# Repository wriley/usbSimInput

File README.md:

# usbSimInput

This project is a 128 button USB HID joystick based on an open source USB game controller adapter by Raphaël Assénat.
http://www.raphnet-tech.com/products/nes2usb/

I use it to interface a lot of switches to a flight simulator but you could use it for anything that requires a lot of buttons.

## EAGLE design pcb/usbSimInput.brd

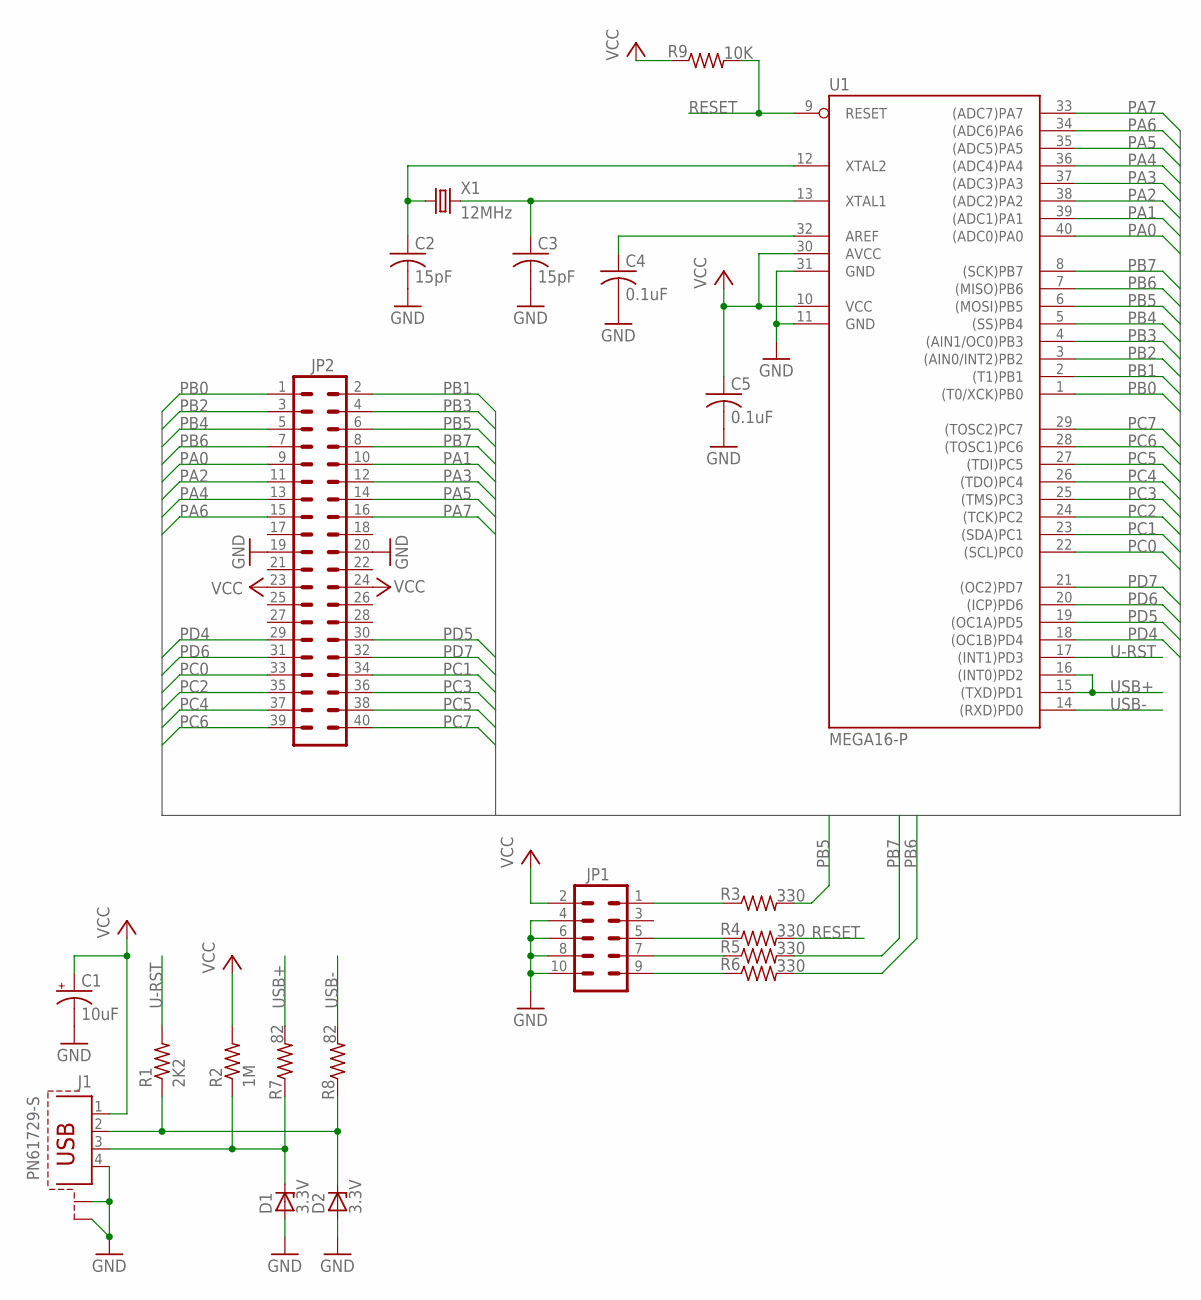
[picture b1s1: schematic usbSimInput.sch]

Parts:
C1: 10uF; E2,5-5
C2, C3: 15pF; C025-024X044
C4, C5: 0.1uF; C050-025X075
D1, D2: 3.3V; ZDIO-5
J1: PN61729-S
JP1: ML10
JP2: MA20-2
R1: 2K2; 0207/7
R2: 1M; 0207/7
R3, R4, R5, R6: 330; 0207/7
R7, R8: 82; 0207/7
R9: 10K; 0207/7
U1: MEGA16-P; DIL40
X1: 12MHz; HC49U-V

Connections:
GND: C1.-, C2.2, C3.2, C4.2, C5.2, D1.A, D2.A, J1.4, J1.S1, J1.S2, JP1.4, JP1.6, JP1.8, JP1.10, JP2.19, JP2.20, U1.11 (GND), U1.31 (GND)
unnamed: JP1.1, R3.1
unnamed: JP1.5, R4.1
unnamed: JP1.7, R5.1
unnamed: JP1.9, R6.1
unnamed: C3.1, U1.13 (XTAL1), X1.2
unnamed: C2.1, U1.12 (XTAL2), X1.1
unnamed: D2.C, J1.2, R1.1, R8.1
unnamed: C4.1, U1.32 (AREF)
unnamed: D1.C, J1.3, R2.1, R7.1
PA0: JP2.9, U1.40 ((ADC0)PA0)
PA1: JP2.10, U1.39 ((ADC1)PA1)
PA2: JP2.11, U1.38 ((ADC2)PA2)
PA3: JP2.12, U1.37 ((ADC3)PA3)
PA4: JP2.13, U1.36 ((ADC4)PA4)
PA5: JP2.14, U1.35 ((ADC5)PA5)
PA6: JP2.15, U1.34 ((ADC6)PA6)
PA7: JP2.16, U1.33 ((ADC7)PA7)
PB0: JP2.1, U1.1 ((T0/XCK)PB0)
PB1: JP2.2, U1.2 ((T1)PB1)
PB2: JP2.3, U1.3 ((AIN0/INT2)PB2)
PB3: JP2.4, U1.4 ((AIN1/OC0)PB3)
PB4: JP2.5, U1.5 ((SS)PB4)
PB5: JP2.6, R3.2, U1.6 ((MOSI)PB5)
PB6: JP2.7, R6.2, U1.7 ((MISO)PB6)
PB7: JP2.8, R5.2, U1.8 ((SCK)PB7)
PC0: JP2.33, U1.22 ((SCL)PC0)
PC1: JP2.34, U1.23 ((SDA)PC1)
PC2: JP2.35, U1.24 ((TCK)PC2)
PC3: JP2.36, U1.25 ((TMS)PC3)
PC4: JP2.37, U1.26 ((TDO)PC4)
PC5: JP2.38, U1.27 ((TDI)PC5)
PC6: JP2.39, U1.28 ((TOSC1)PC6)
PC7: JP2.40, U1.29 ((TOSC2)PC7)
PD4: JP2.29, U1.18 ((OC1B)PD4)
PD5: JP2.30, U1.19 ((OC1A)PD5)
PD6: JP2.31, U1.20 ((ICP)PD6)
PD7: JP2.32, U1.21 ((OC2)PD7)
RESET: R4.2, R9.2, U1.9 (RESET)
U-RST: R1.2, U1.17 ((INT1)PD3)
USB+: R7.2, U1.15 ((TXD)PD1), U1.16 ((INT0)PD2)
USB-: R8.2, U1.14 ((RXD)PD0)
VCC: C1.+, C5.1, J1.1, JP1.2, JP2.23, JP2.24, R2.2, R9.1, U1.10 (VCC), U1.30 (AVCC)

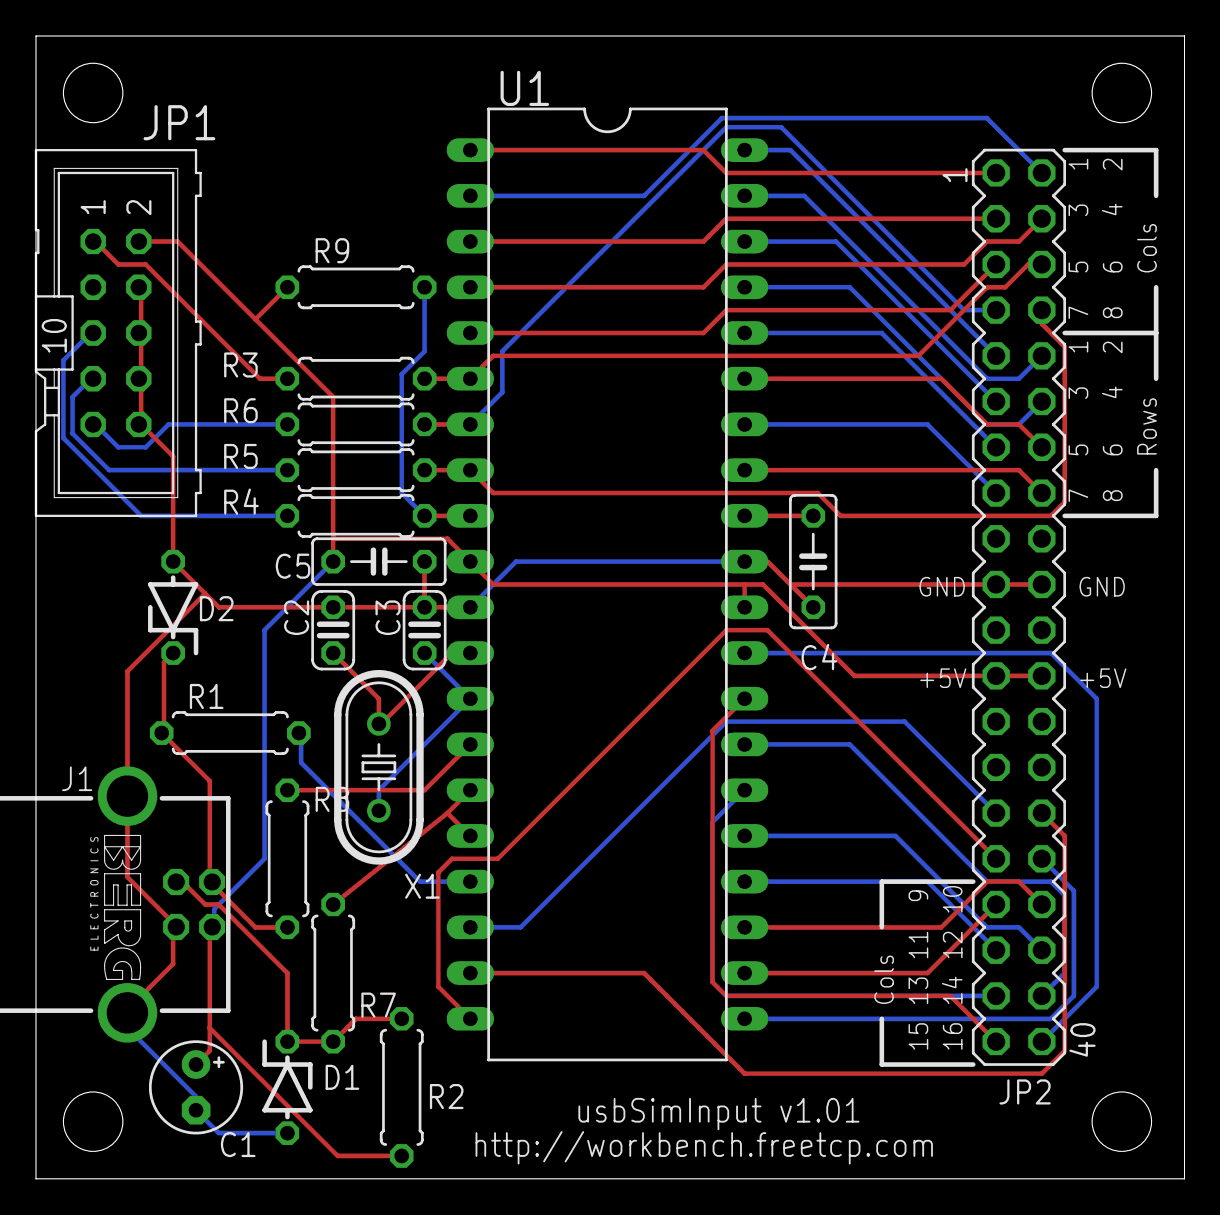
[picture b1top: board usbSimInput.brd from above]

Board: 2 copper layers, 63.8 x 63.5 mm, 25 parts (0 on the bottom side), 43 nets.

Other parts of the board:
U$1, U$2, U$3, U$4: STAND-OFF

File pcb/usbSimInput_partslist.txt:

Partlist

Exported from usbSimInput.sch at 3/3/2012 2:18:12 PM

EAGLE Version 6.1.0 Copyright (c) 1988-2012 CadSoft

Assembly variant: 

Part     Value          Device          Package      Library  Sheet

C1       10uF           CPOL-USE2.5-5   E2,5-5       rcl      1
C2       15pF           C-US025-024X044 C025-024X044 rcl      1
C3       15pF           C-US025-024X044 C025-024X044 rcl      1
C4       0.1uF          C-US050-025X075 C050-025X075 rcl      1
C5       0.1uF          C-US050-025X075 C050-025X075 rcl      1
D1       3.3V           ZENER-DIODEZD-5 ZDIO-5       diode    1
D2       3.3V           ZENER-DIODEZD-5 ZDIO-5       diode    1
J1                      PN61729-S       PN61729-S    con-berg 1
JP1                     ML10            ML10         con-ml   1
JP2                     MA20-2          MA20-2       con-lstb 1
R1       2K2            R-US_0207/7     0207/7       resistor 1
R2       4K7            R-US_0207/7     0207/7       resistor 1
R3       330            R-US_0207/7     0207/7       resistor 1
R4       330            R-US_0207/7     0207/7       resistor 1
R5       330            R-US_0207/7     0207/7       resistor 1
R6       330            R-US_0207/7     0207/7       resistor 1
R7       82             R-US_0207/7     0207/7       resistor 1
R8       82             R-US_0207/7     0207/7       resistor 1
U1       MEGA16-P       MEGA16-P        DIL40        atmel    1
X1       12MHz          CRYSTALHC49U-V  HC49U-V      crystal  1

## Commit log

2011-04-29 initial directory structure
2011-04-29 started schematic
2011-04-29 first stab at completed schematic and a 2 layer board
2011-05-01 usbSimInput.sch: changed to ExpressPCB
2011-05-01 usbSimInput.sch: started button connections
2011-05-02 usbSimInput.sch: finished button connections
2011-05-02 usbSimInput.pcb: started board layout
2011-06-01 moved input connections to separate board
2011-06-01 usbSimInput.sch: changed ISP connector from 6-pin to 10-pin usbSimInput.pcb: started layout
2011-06-03 pcb layout work changed from 34-pin connector to 3 8-pin connectors
2011-06-10 usbSimInput.sch: changed from 10-pin to 6-pin ISP connector, added 4-pin header for unused MCU pins usbSimInput.pcb: finished layout, needs testing
2011-06-10 usbSimInput.sch: changed PORTC resistors to resistor network usbSimInput.pcb: minor trace tweaks, SIP resistor network for PORTC
2012-01-23 Changed from ExpressPCB to Eagle
2012-01-23 added firmware dir. this code is COMPLETELY UNTESTED!!!
2012-01-24 Layout tweaks for Seeed DRU
2012-01-24 added gerber output (Seeed CAM)
2012-01-25 added rows and cols to silkscreen created povray files
2012-01-25 updated gerbers for silkscreen changes
2012-01-26 connected unused PORTD pins to header made board smaller
2012-01-26 fixed orientation of usb jack in povray
2012-03-02 Moved firmware code to AVR Studio 5.1 solution
2012-03-04 pcb rev to 1.01, fixed several errors and tweaked firmware enumerates
2012-03-06 firmware working as 64-button HID joystick
2012-03-06 rewrote based on this project: http://www.raphnet-tech.com/products/usb_game12/index.php Nes/Snes/Genesis/SMS/Atari to USB Copyright (C) 2006-2007 Raphaël Assénat
2012-03-07 Mostly working 128 button firmware. Buttons sometime "stick" on
2012-03-09 fixed AREF->VCC error
2012-03-09 Working with 128 buttons
2015-03-06 updated to AVR Studio 6
2015-03-06 updated gerbers for pcb v1.0.1
2015-03-06 file mode fix for gerbers
2015-03-06 edited USB connector silkscreen
2015-03-06 gerbers for seeedstudio
2015-03-06 added .gitignore
2015-03-06 removed firmware/usbSimInput.atsuo

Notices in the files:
parts and their libraries:
SparkFun: Licensing: CC v3.0 Share-Alike You are welcome to use this library for commercial purposes.
